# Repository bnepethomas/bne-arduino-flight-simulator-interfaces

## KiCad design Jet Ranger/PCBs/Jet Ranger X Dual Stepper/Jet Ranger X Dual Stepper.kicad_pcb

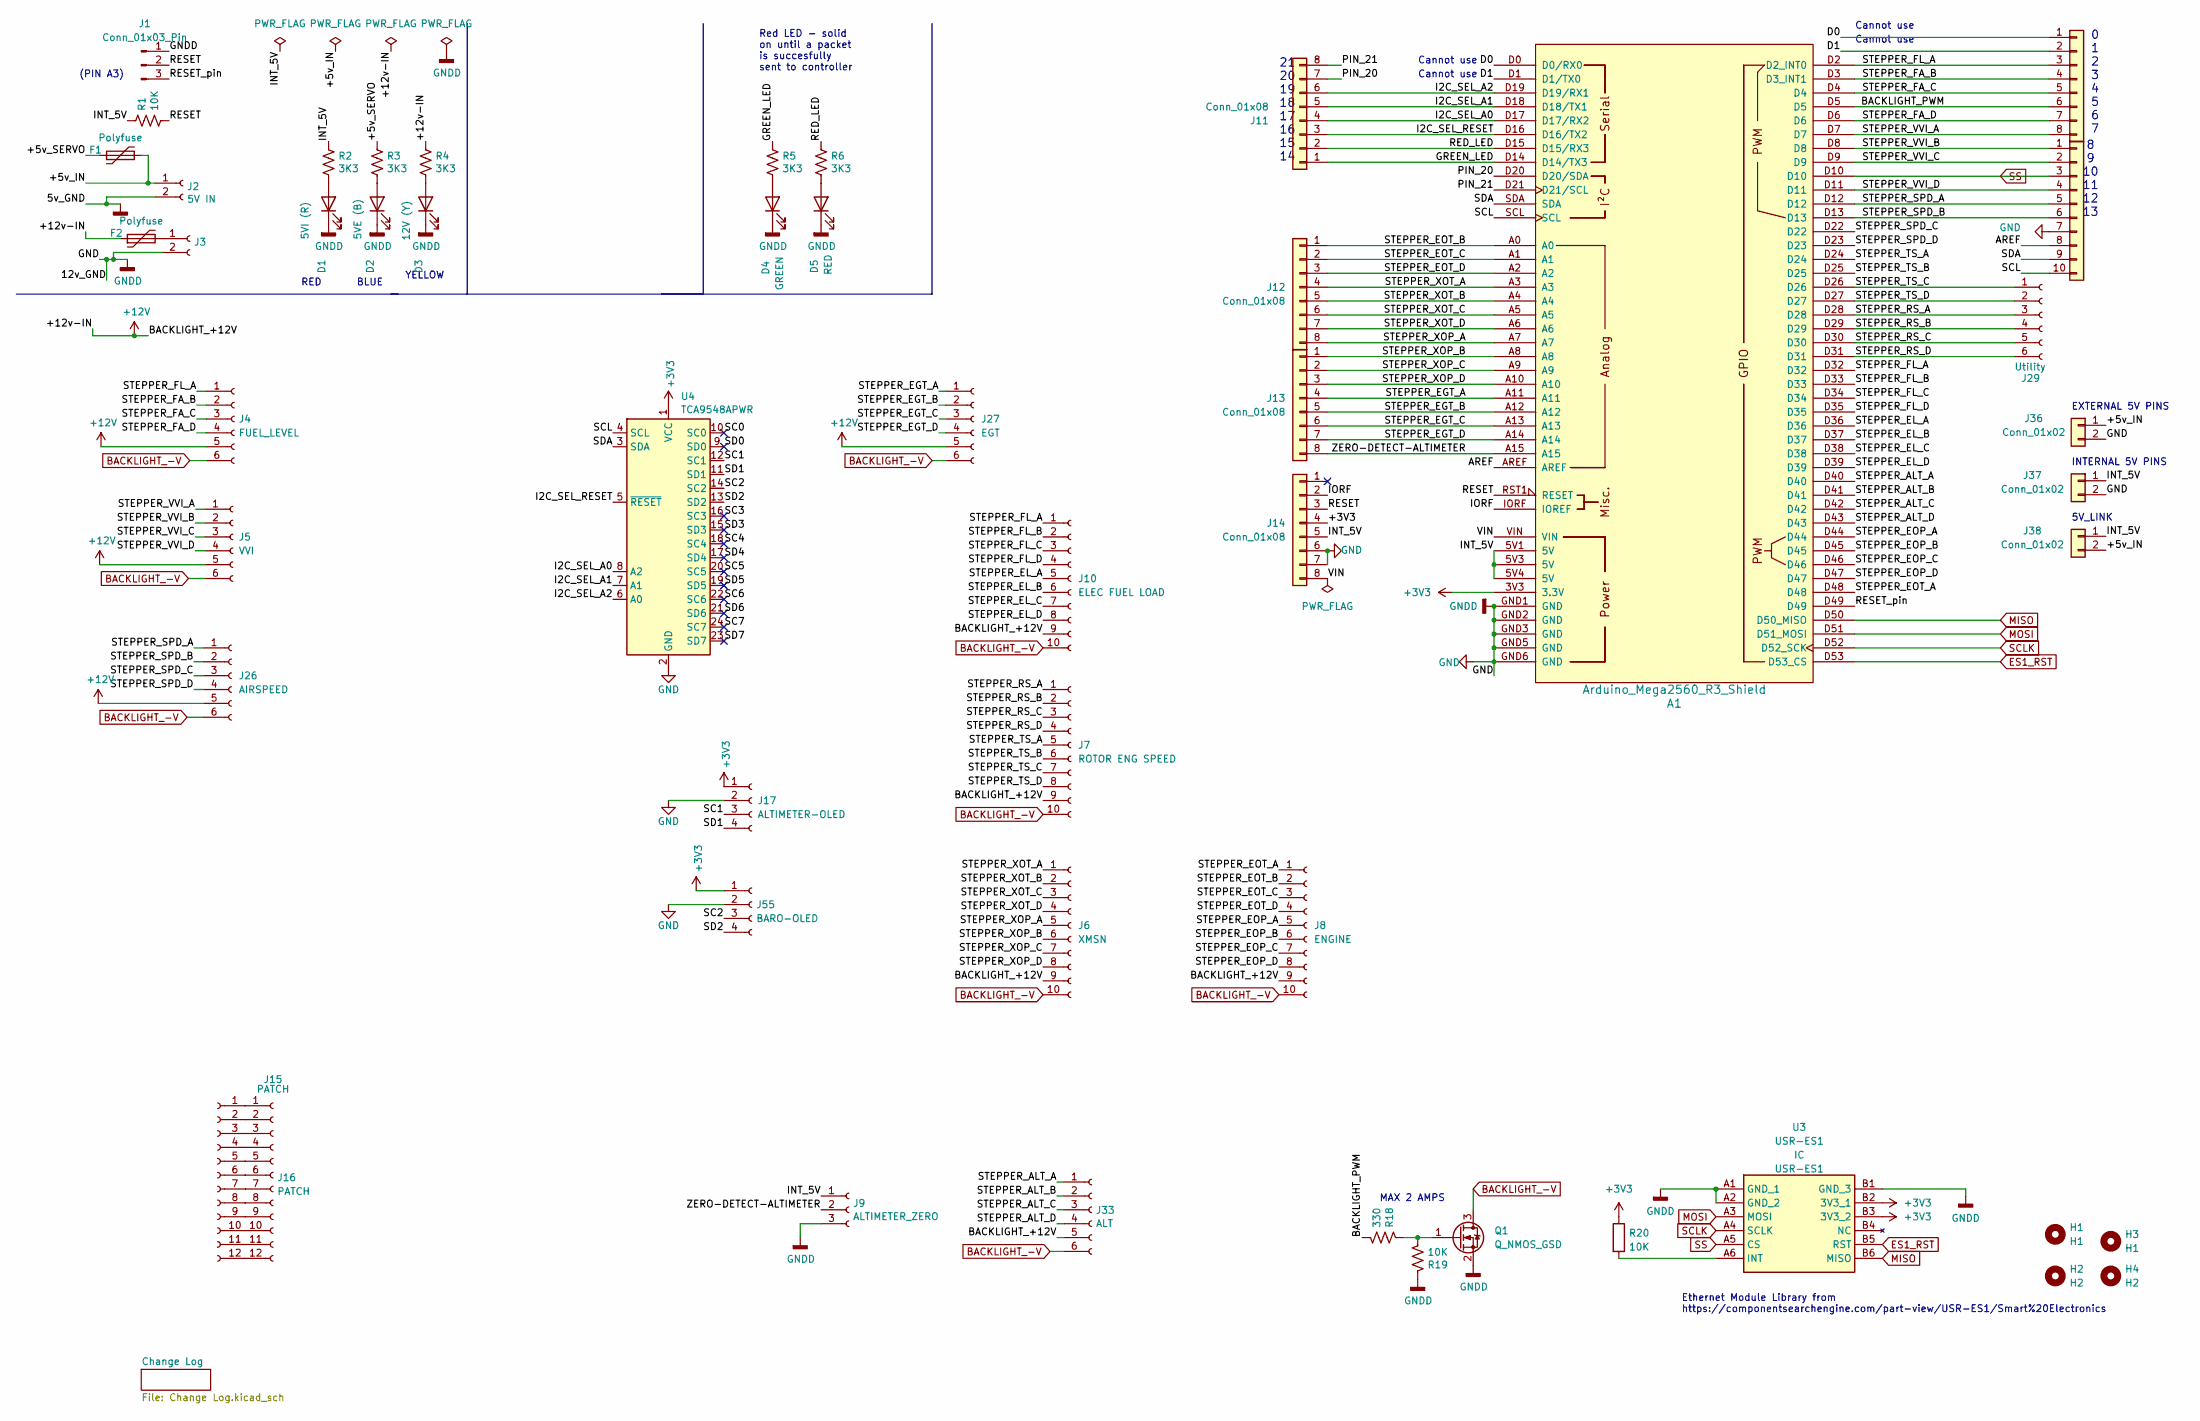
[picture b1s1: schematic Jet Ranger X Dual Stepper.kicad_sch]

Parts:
A1: Arduino_Mega2560_R3_Shield
D1: 5VI (R); LED_D3.0mm
D2: 5VE (B); LED_D3.0mm
D3: 12V (Y); LED_D3.0mm
D4: GREEN; LED_D3.0mm
D5: RED; LED_D3.0mm
F1, F2: Polyfuse; Fuse_Littelfuse_395Series
H1, H3: H1; MountingHole_3.2mm_M3
H2, H4: H2; MountingHole_3.2mm_M3
J1: Conn_01x03_Pin; PinHeader_1x03_P2.54mm_Vertical
J2: 5V IN; BarrelJack_Horizontal
J3: STEPPER IN 12-20VDC; BarrelJack_Horizontal
J4: FUEL_LEVEL; Molex_KK-254_AE-6410-06A_1x06_P2.54mm_Vertical
J5: VVI; Molex_KK-254_AE-6410-06A_1x06_P2.54mm_Vertical
J6: XMSN; Molex_KK-254_AE-6410-10A_1x10_P2.54mm_Vertical
J7: ROTOR ENG SPEED; Molex_KK-254_AE-6410-10A_1x10_P2.54mm_Vertical
J8: ENGINE; Molex_KK-254_AE-6410-10A_1x10_P2.54mm_Vertical
J9: ALTIMETER_ZERO; Molex_KK-254_AE-6410-03A_1x03_P2.54mm_Vertical
J10: ELEC FUEL LOAD; Molex_KK-254_AE-6410-10A_1x10_P2.54mm_Vertical
J11, J12, J13, J14, J34: Conn_01x08; PinHeader_1x08_P2.54mm_Vertical
J15, J16: PATCH; PinSocket_1x12_P2.54mm_Vertical
J17: ALTIMETER-OLED; Molex_KK-254_AE-6410-04A_1x04_P2.54mm_Vertical
J26: AIRSPEED; Molex_KK-254_AE-6410-06A_1x06_P2.54mm_Vertical
J27: EGT; Molex_KK-254_AE-6410-06A_1x06_P2.54mm_Vertical
J29: Utility; PinHeader_1x06_P2.54mm_Vertical
J33: ALT; Molex_KK-254_AE-6410-06A_1x06_P2.54mm_Vertical
J35: Conn_01x10; PinHeader_1x10_P2.54mm_Vertical
J36, J37, J38: Conn_01x02; PinHeader_1x02_P2.54mm_Vertical
J55: BARO-OLED; Molex_KK-254_AE-6410-04A_1x04_P2.54mm_Vertical
Q1: Q_NMOS_GSD; TO-220-3_Vertical
R1, R19, R20: 10K; R_Axial_DIN0207_L6.3mm_D2.5mm_P2.54mm_Vertical
R2, R3, R4, R5, R6: 3K3; R_Axial_DIN0207_L6.3mm_D2.5mm_P2.54mm_Vertical
R18: 330; R_Axial_DIN0207_L6.3mm_D2.5mm_P2.54mm_Vertical
U3: USR-ES1; USRES1; Manufacturer_Part_Number USR-ES1
U4: TCA9548APWR; DIP-24_TCA9548A

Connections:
+3V3: A1.3V3 (3.3V), J14.4, J17.1, J55.1, R20.1, U3.B2 (3V3_1), U3.B3 (3V3_2), U4.1 (VCC)
+12V: F2.1, J4.5, J5.5, J6.9, J7.9, J8.9, J10.9, J26.5, J27.5, J33.5, R4.1
/+5v_IN: F1.2, J2.1, J36.1, J38.2
/+5v_SERVO: F1.1, R3.1
/AREF: A1.AREF, J35.8
/BACKLIGHT_PWM: A1.D5, J34.6, R18.2
/D0: A1.D0 (D0/RX0), J34.1
/D1: A1.D1 (D1/TX0), J34.2
/GREEN_LED: A1.D14 (D14/TX3), J11.1, R5.1
/I2C_SEL_A0: A1.D17 (D17/RX2), J11.4, U4.8 (A2)
/I2C_SEL_A1: A1.D18 (D18/TX1), J11.5, U4.7 (A1)
/I2C_SEL_A2: A1.D19 (D19/RX1), J11.6, U4.6 (A0)
/I2C_SEL_RESET: A1.D16 (D16/TX2), J11.3, U4.5 (~RESET)
/INT_5V: A1.5V1 (5V), A1.5V3 (5V), A1.5V4 (5V), J9.1, J14.5, J37.1, J38.1, R1.1, R2.1
/IORF: A1.IORF (IOREF), J14.2
/PIN_20: A1.D20 (D20/SDA), J11.7
/PIN_21: A1.D21 (D21/SCL), J11.8
/RED_LED: A1.D15 (D15/RX3), J11.2, R6.1
/RESET: A1.RST1 (RESET), J1.2, J14.3, R1.2
/RESET_pin: A1.D49, J1.3
/SC0: U4.10 (SC0)
/SC1: J17.3, U4.12 (SC1)
/SC2: J55.3, U4.14 (SC2)
/SC3: U4.16 (SC3)
/SC4: U4.18 (SC4)
/SC5: U4.20 (SC5)
/SC6: U4.22 (SC6)
/SC7: U4.24 (SC7)
/SCL: A1.SCL, J35.10, U4.4 (SCL)
/SD0: U4.9 (SD0)
/SD1: J17.4, U4.11 (SD1)
/SD2: J55.4, U4.13 (SD2)
/SD3: U4.15 (SD3)
/SD4: U4.17 (SD4)
/SD5: U4.19 (SD5)
/SD6: U4.21 (SD6)
/SD7: U4.23 (SD7)
/SDA: A1.SDA, J35.9, U4.3 (SDA)
/STEPPER_ALT_A: A1.D40, J33.1
/STEPPER_ALT_B: A1.D41, J33.2
/STEPPER_ALT_C: A1.D42, J33.3
/STEPPER_ALT_D: A1.D43, J33.4
/STEPPER_EGT_A: A1.A11, J13.4, J27.1
/STEPPER_EGT_B: A1.A12, J13.5, J27.2
/STEPPER_EGT_C: A1.A13, J13.6, J27.3
/STEPPER_EGT_D: A1.A14, J13.7, J27.4
/STEPPER_EL_A: A1.D36, J10.5
/STEPPER_EL_B: A1.D37, J10.6
/STEPPER_EL_C: A1.D38, J10.7
/STEPPER_EL_D: A1.D39, J10.8
/STEPPER_EOP_A: A1.D44, J8.5
/STEPPER_EOP_B: A1.D45, J8.6
/STEPPER_EOP_C: A1.D46, J8.7
/STEPPER_EOP_D: A1.D47, J8.8
/STEPPER_EOT_A: A1.D48, J8.1
/STEPPER_EOT_B: A1.A0, J8.2, J12.1
/STEPPER_EOT_C: A1.A1, J8.3, J12.2
/STEPPER_EOT_D: A1.A2, J8.4, J12.3
/STEPPER_FA_B: A1.D3 (D3_INT1), J4.2, J34.4
/STEPPER_FA_C: A1.D4, J4.3, J34.5
/STEPPER_FA_D: A1.D6, J4.4, J34.7
/STEPPER_FL_A: A1.D2 (D2_INT0), A1.D32, J4.1, J10.1, J34.3
/STEPPER_FL_B: A1.D33, J10.2
/STEPPER_FL_C: A1.D34, J10.3
/STEPPER_FL_D: A1.D35, J10.4
/STEPPER_RS_A: A1.D28, J7.1, J29.3
/STEPPER_RS_B: A1.D29, J7.2, J29.4
/STEPPER_RS_C: A1.D30, J7.3, J29.5
/STEPPER_RS_D: A1.D31, J7.4, J29.6
/STEPPER_SPD_A: A1.D12, J26.1, J35.5
/STEPPER_SPD_B: A1.D13, J26.2, J35.6
/STEPPER_SPD_C: A1.D22, J26.3
/STEPPER_SPD_D: A1.D23, J26.4
/STEPPER_TS_A: A1.D24, J7.5
/STEPPER_TS_B: A1.D25, J7.6
/STEPPER_TS_C: A1.D26, J7.7, J29.1
/STEPPER_TS_D: A1.D27, J7.8, J29.2
/STEPPER_VVI_A: A1.D7, J5.1, J34.8
/STEPPER_VVI_B: A1.D8, J5.2, J35.1
/STEPPER_VVI_C: A1.D9, J5.3, J35.2
/STEPPER_VVI_D: A1.D11, J5.4, J35.4
/STEPPER_XOP_A: A1.A7, J6.5, J12.8
/STEPPER_XOP_B: A1.A8, J6.6, J13.1
/STEPPER_XOP_C: A1.A9, J6.7, J13.2
/STEPPER_XOP_D: A1.A10, J6.8, J13.3
/STEPPER_XOT_A: A1.A3, J6.1, J12.4
/STEPPER_XOT_B: A1.A4, J6.2, J12.5
/STEPPER_XOT_C: A1.A5, J6.3, J12.6
/STEPPER_XOT_D: A1.A6, J6.4, J12.7
/VIN: A1.VIN, J14.8
/ZERO-DETECT-ALTIMETER: A1.A15, J9.2, J13.8
BACKLIGHT_-V: J4.6, J5.6, J6.10, J7.10, J8.10, J10.10, J26.6, J27.6, J33.6, Q1.3 (D)
ES1_RST: A1.D53 (D53_CS), U3.B5 (RST)
GND: A1.GND1 (GND), A1.GND2 (GND), A1.GND3 (GND), A1.GND5 (GND), A1.GND6 (GND), D1.1 (K), D2.1 (K), D3.1 (K), D4.1 (K), D5.1 (K), J1.1, J2.2, J3.2, J9.3, J14.6, J14.7, J17.2, J35.7, J36.2, J37.2, J55.2, Q1.2 (S), R19.1, U3.A1 (GND_1), U3.A2 (GND_2), U3.B1 (GND_3), U4.2 (GND)
MISO: A1.D50 (D50_MISO), U3.B6 (MISO)
MOSI: A1.D51 (D51_MOSI), U3.A3 (MOSI)
unnamed: D1.2 (A), R2.2
unnamed: D2.2 (A), R3.2
unnamed: D3.2 (A), R4.2
unnamed: D4.2 (A), R5.2
unnamed: D5.2 (A), R6.2
unnamed: F2.2, J3.1
unnamed: J15.1, J16.1
unnamed: J15.2, J16.2
unnamed: J15.3, J16.3
unnamed: J15.4, J16.4
unnamed: J15.5, J16.5
unnamed: J15.6, J16.6
unnamed: J15.7, J16.7
unnamed: J15.8, J16.8
unnamed: J15.9, J16.9
unnamed: J15.10, J16.10
unnamed: J15.11, J16.11
unnamed: J15.12, J16.12
unnamed: Q1.1 (G), R18.1, R19.2
unnamed: R20.2, U3.A6 (INT)
SCLK: A1.D52 (D52_SCK), U3.A4 (SCLK)
SS: A1.D10, J35.3, U3.A5 (CS)

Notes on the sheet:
YELLOW
MAX 2 AMPS
BLUE
INTERNAL 5V PINS
Ethernet Module Library from https://componentsearchengine.com/part-view/USR-ES1/Smart%20Electronics
Cannot use
RED
(PIN A3)
0 1 2 3 4 5 6 7
Red LED - solid on until a packet is succesfully sent to controller
5V_LINK
21 20 19 18 17 16 15 14
EXTERNAL 5V PINS
8 9 10 11 12 13

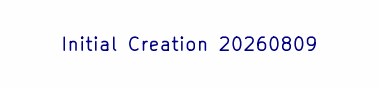
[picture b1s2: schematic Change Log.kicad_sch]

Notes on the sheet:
Initial Creation 20260809

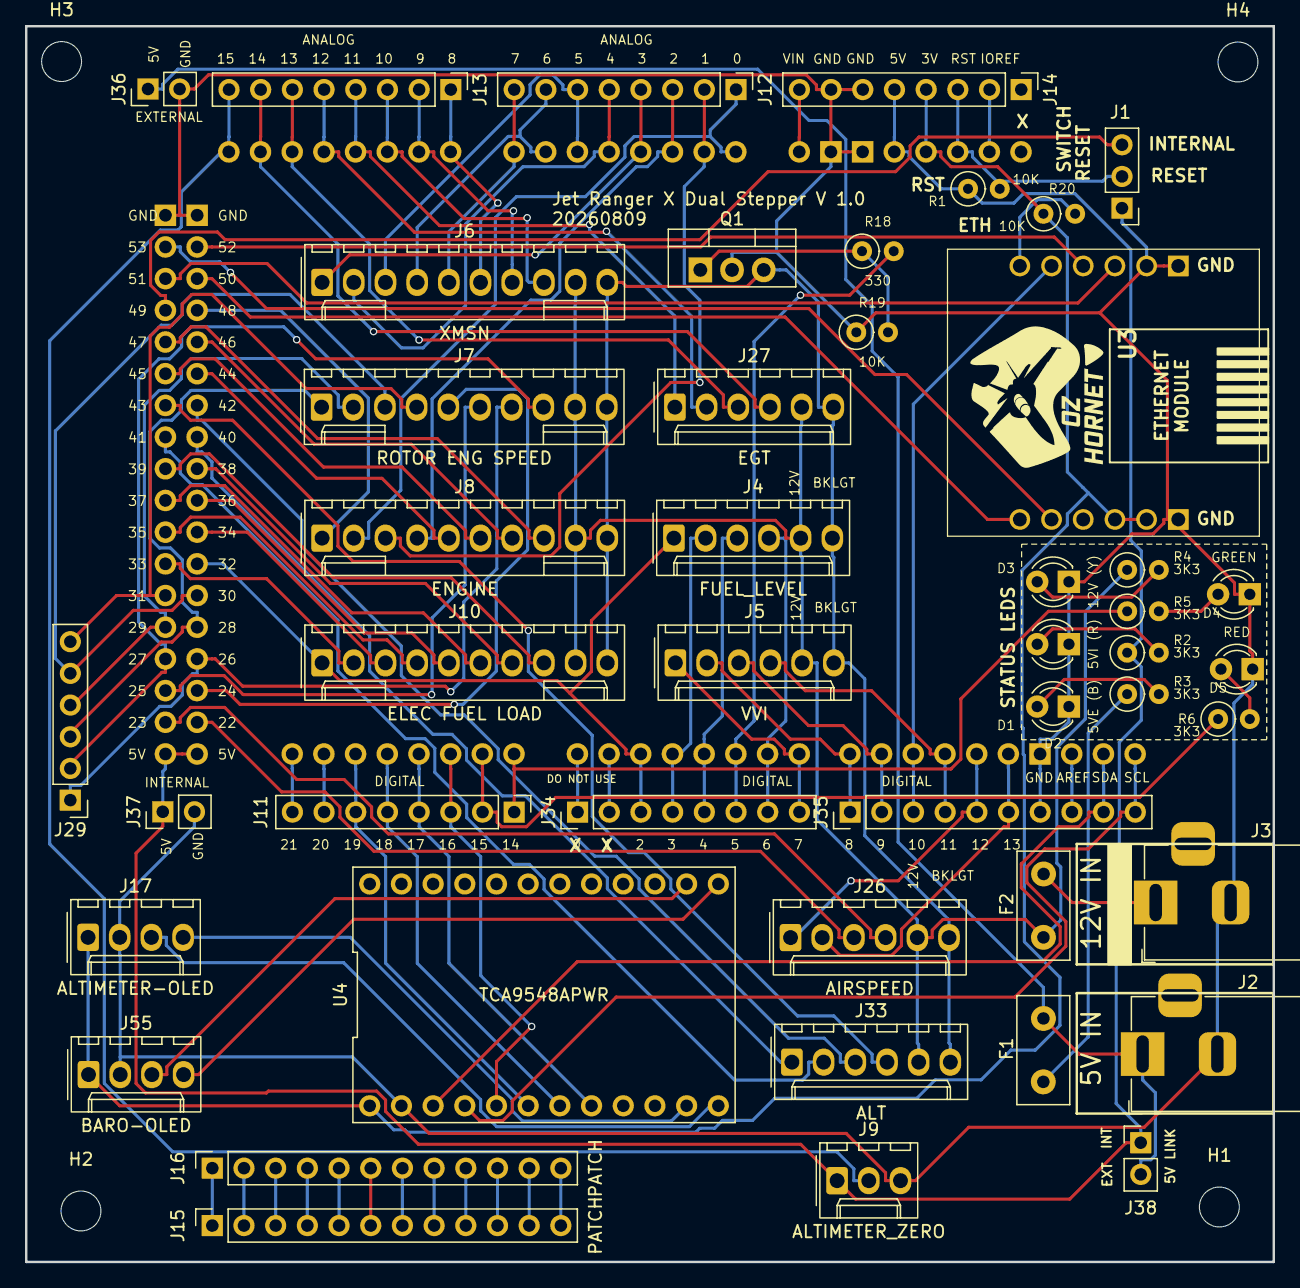
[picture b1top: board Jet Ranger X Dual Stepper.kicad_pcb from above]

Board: 2 copper layers, 100.0 x 99.1 mm, 51 parts (0 on the bottom side), 106 nets.

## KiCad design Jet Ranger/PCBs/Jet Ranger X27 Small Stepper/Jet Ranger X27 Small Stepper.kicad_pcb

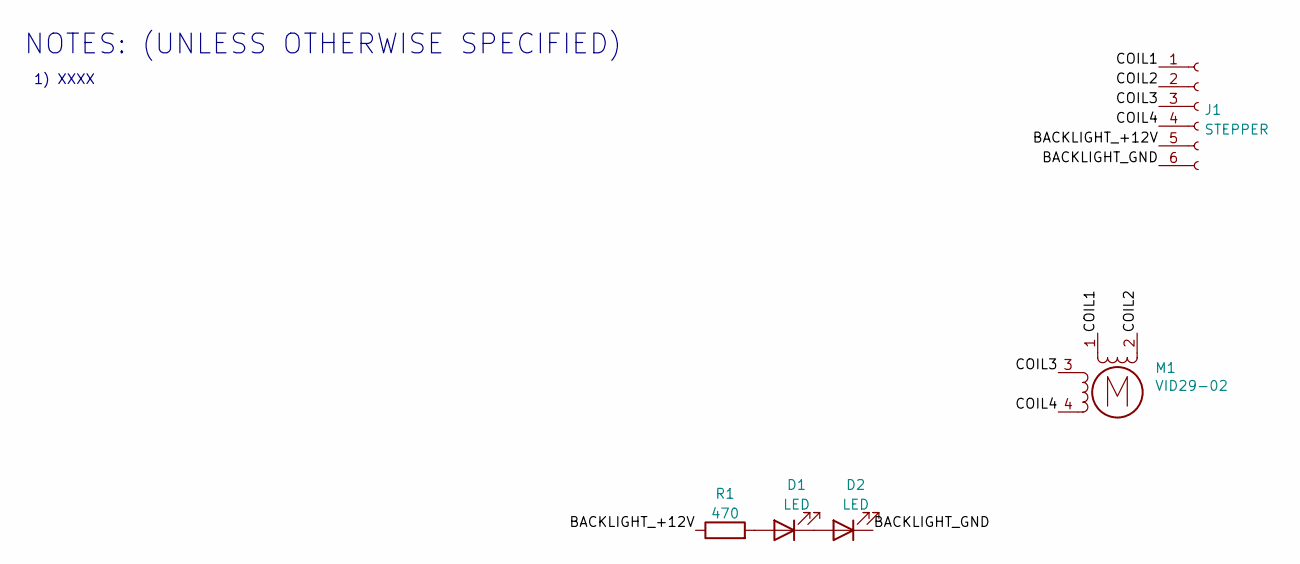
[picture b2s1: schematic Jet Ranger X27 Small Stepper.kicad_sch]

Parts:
D1, D2: LED; LED_D3.0mm
J1: STEPPER; Molex_KK-254_AE-6410-06A_1x06_P2.54mm_Vertical
M1: VID29-02
R1: 470; R_Axial_DIN0204_L3.6mm_D1.6mm_P1.90mm_Vertical

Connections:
/BACKLIGHT_+12V: J1.5, R1.1
/BACKLIGHT_GND: D2.1 (K), J1.6
/COIL1: J1.1, M1.1
/COIL2: J1.2, M1.2 (-)
/COIL3: J1.3, M1.3
/COIL4: J1.4, M1.4
unnamed: D1.2 (A), R1.2
unnamed: D1.1 (K), D2.2 (A)

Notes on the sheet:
1) XXXX
NOTES: (UNLESS OTHERWISE SPECIFIED)

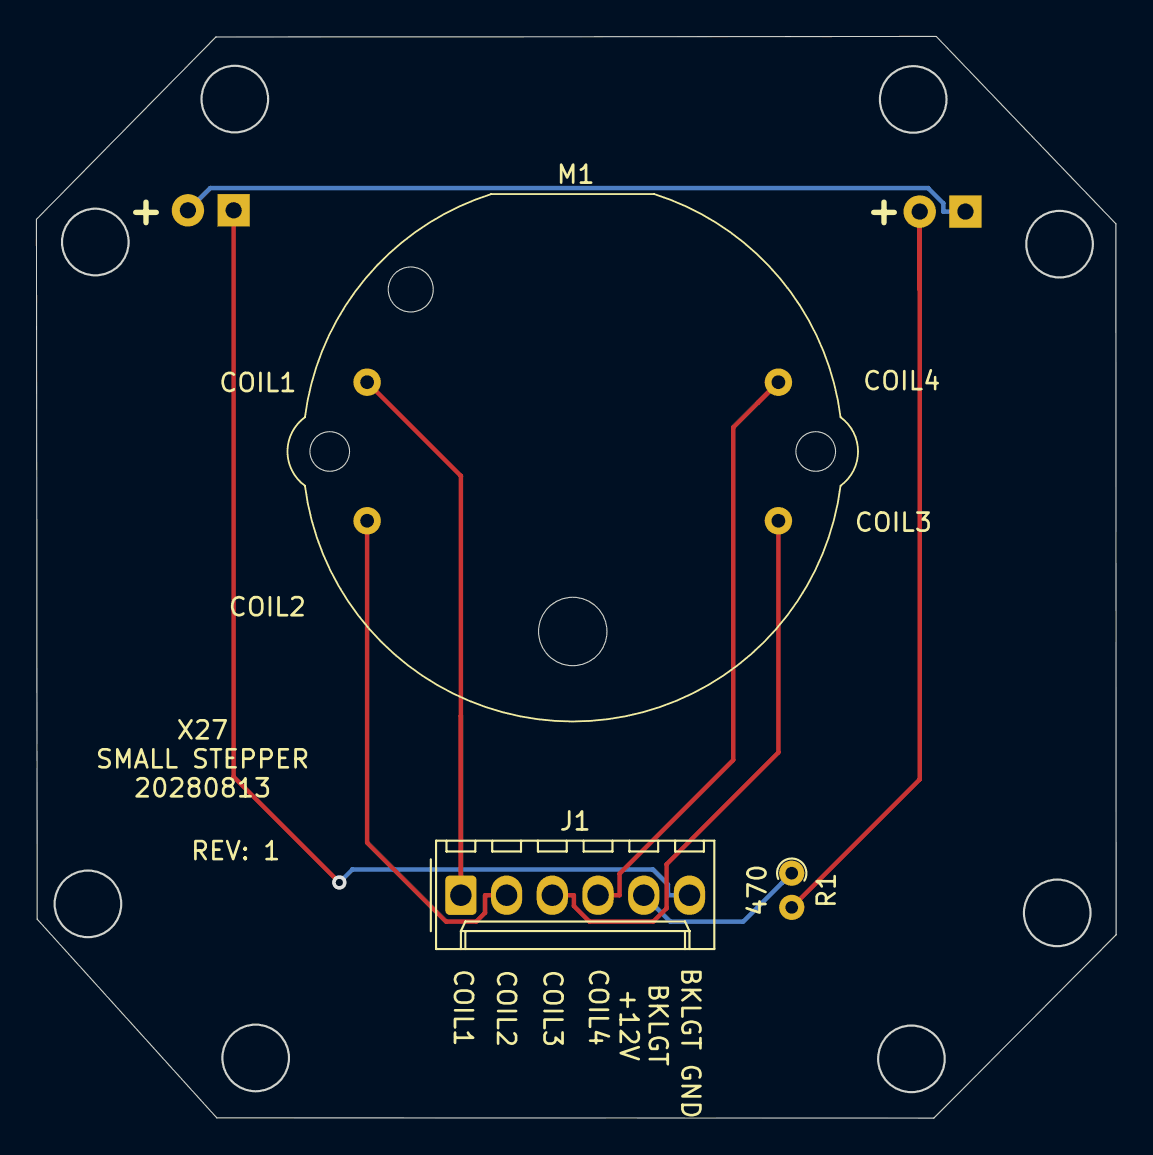
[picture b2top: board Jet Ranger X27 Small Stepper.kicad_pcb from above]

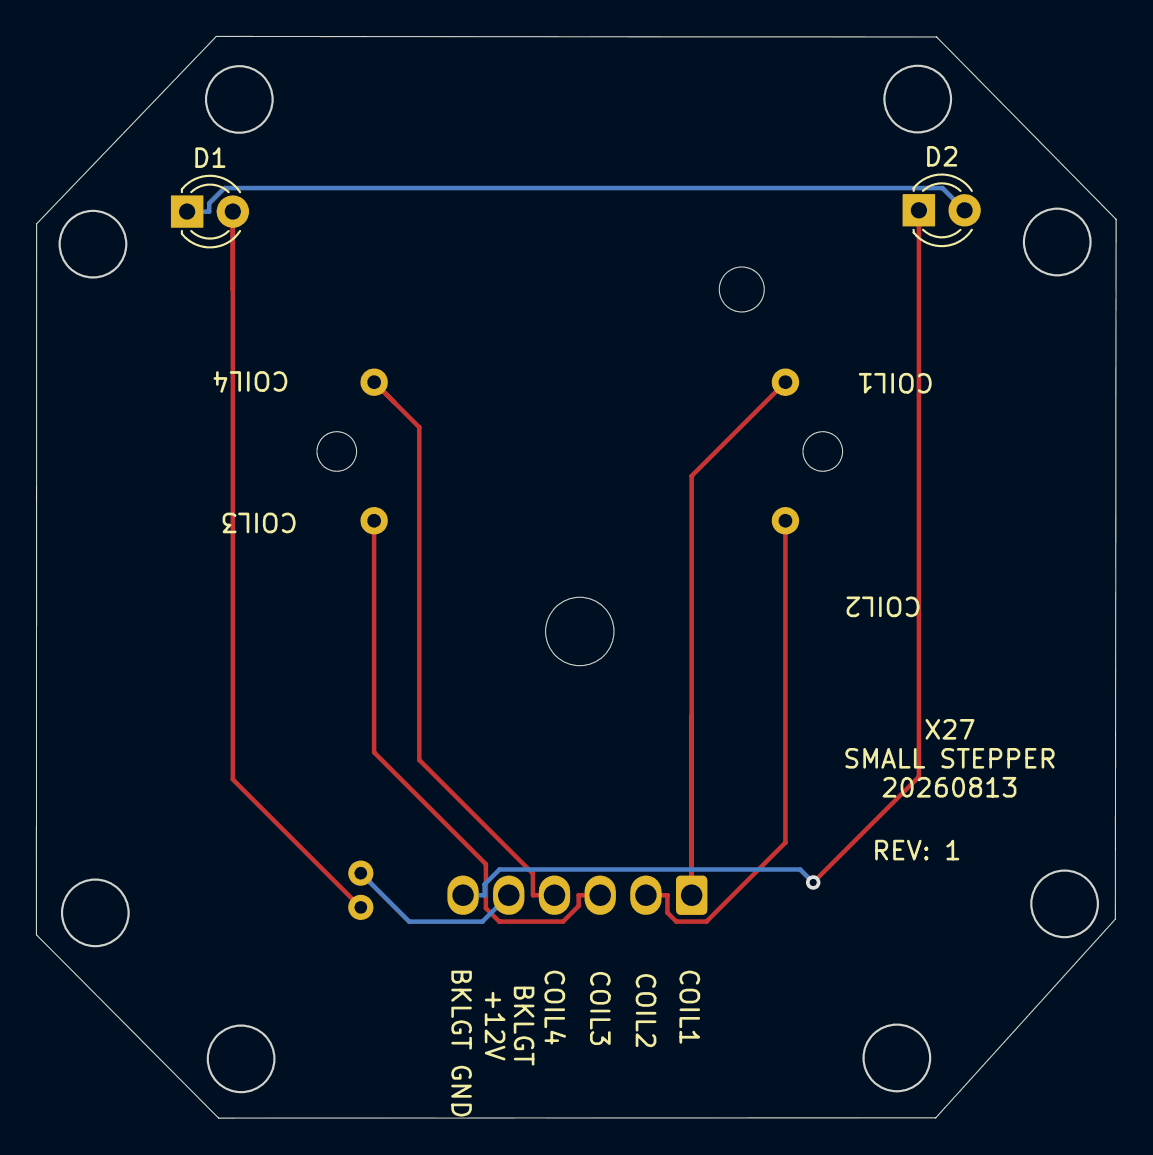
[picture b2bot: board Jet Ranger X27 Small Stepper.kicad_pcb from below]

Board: 2 copper layers, 60.0 x 60.1 mm, 5 parts (2 on the bottom side), 8 nets.

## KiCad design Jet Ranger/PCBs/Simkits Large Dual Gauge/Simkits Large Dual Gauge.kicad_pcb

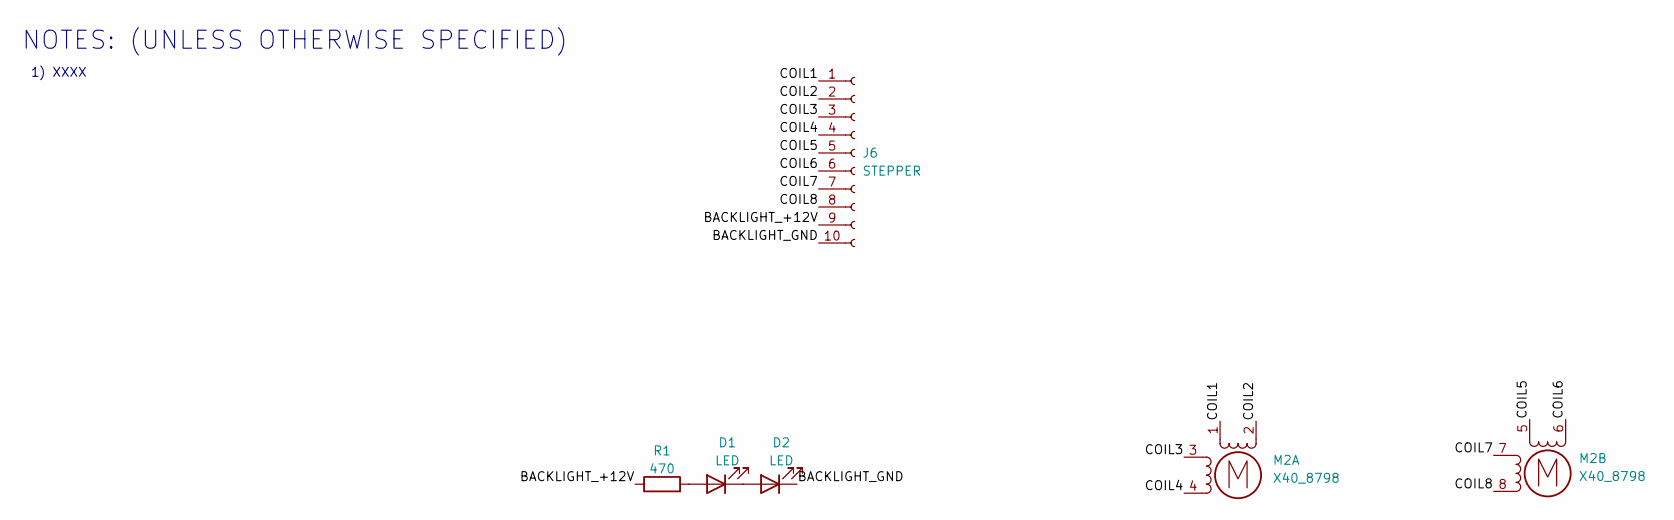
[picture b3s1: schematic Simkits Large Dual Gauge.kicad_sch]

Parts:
D1, D2: LED; LED_D3.0mm
J6: STEPPER; Molex_KK-254_AE-6410-10A_1x10_P2.54mm_Vertical
M2: X40_8798; x40_8798
R1: 470; R_Axial_DIN0204_L3.6mm_D1.6mm_P1.90mm_Vertical

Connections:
/BACKLIGHT_+12V: J6.9, R1.1
/BACKLIGHT_GND: D2.1 (K), J6.10
/COIL1: J6.1, M2.1
/COIL2: J6.2, M2.2 (-)
/COIL3: J6.3, M2.3
/COIL4: J6.4, M2.4
/COIL5: J6.5, M2.5
/COIL6: J6.6, M2.6 (-)
/COIL7: J6.7, M2.7
/COIL8: J6.8, M2.8
unnamed: D1.2 (A), R1.2
unnamed: D1.1 (K), D2.2 (A)

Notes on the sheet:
1) XXXX
NOTES: (UNLESS OTHERWISE SPECIFIED)

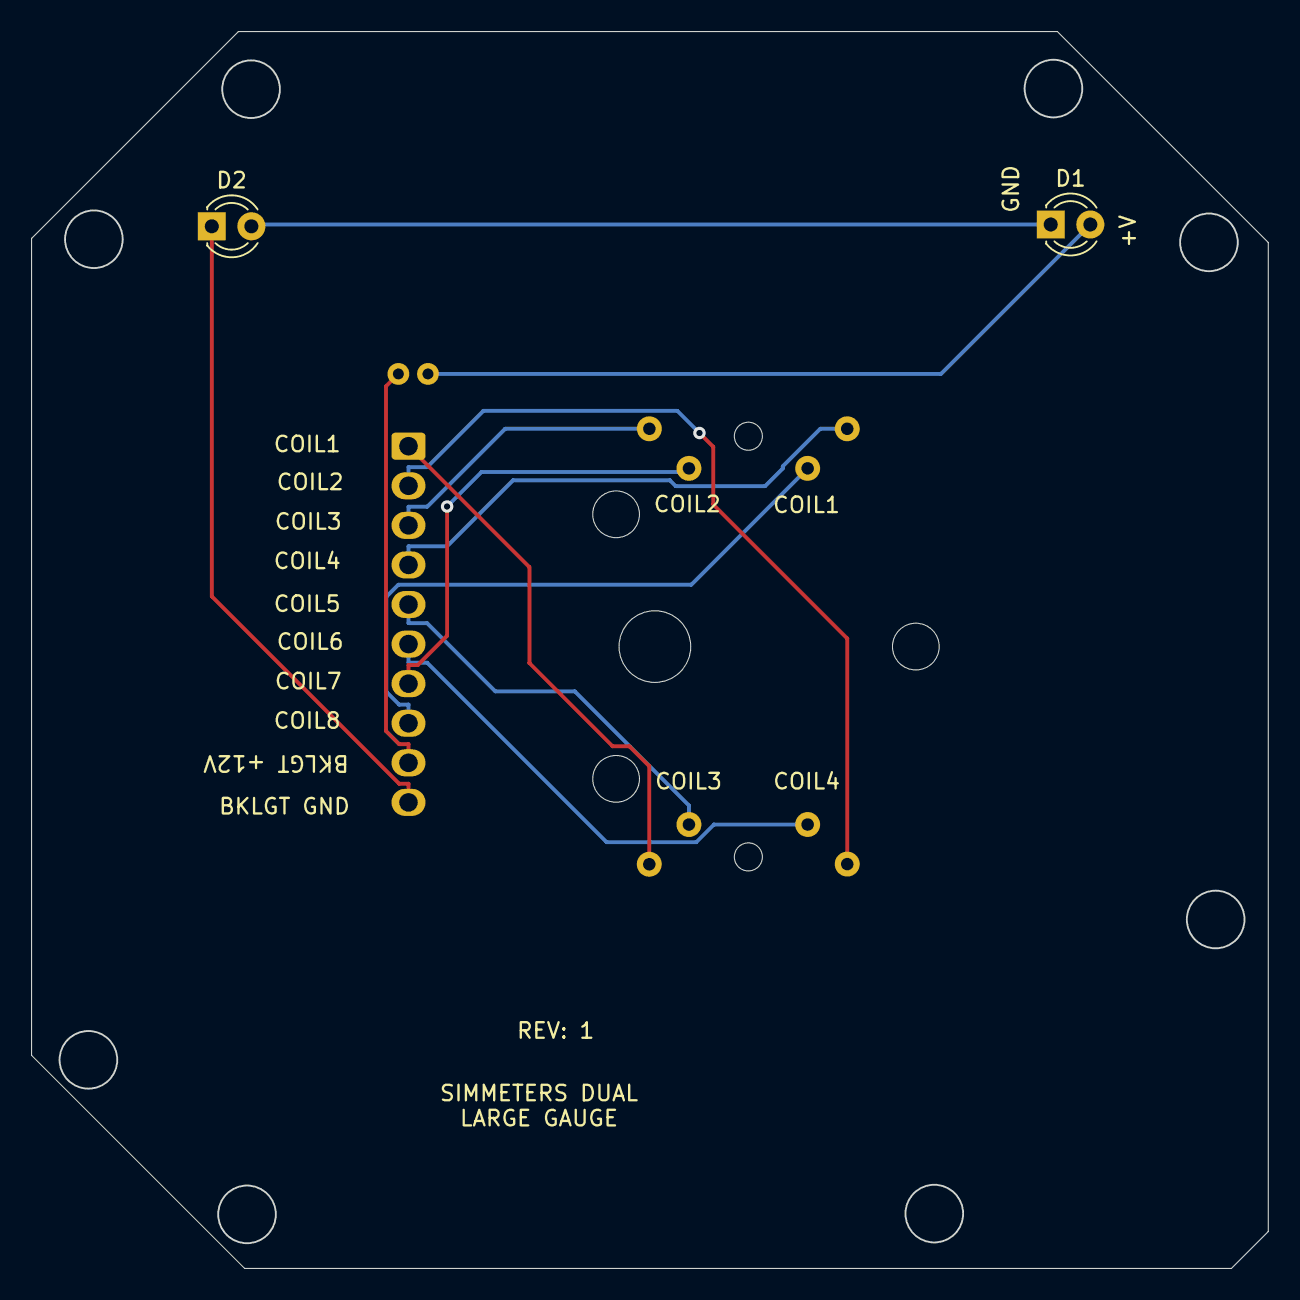
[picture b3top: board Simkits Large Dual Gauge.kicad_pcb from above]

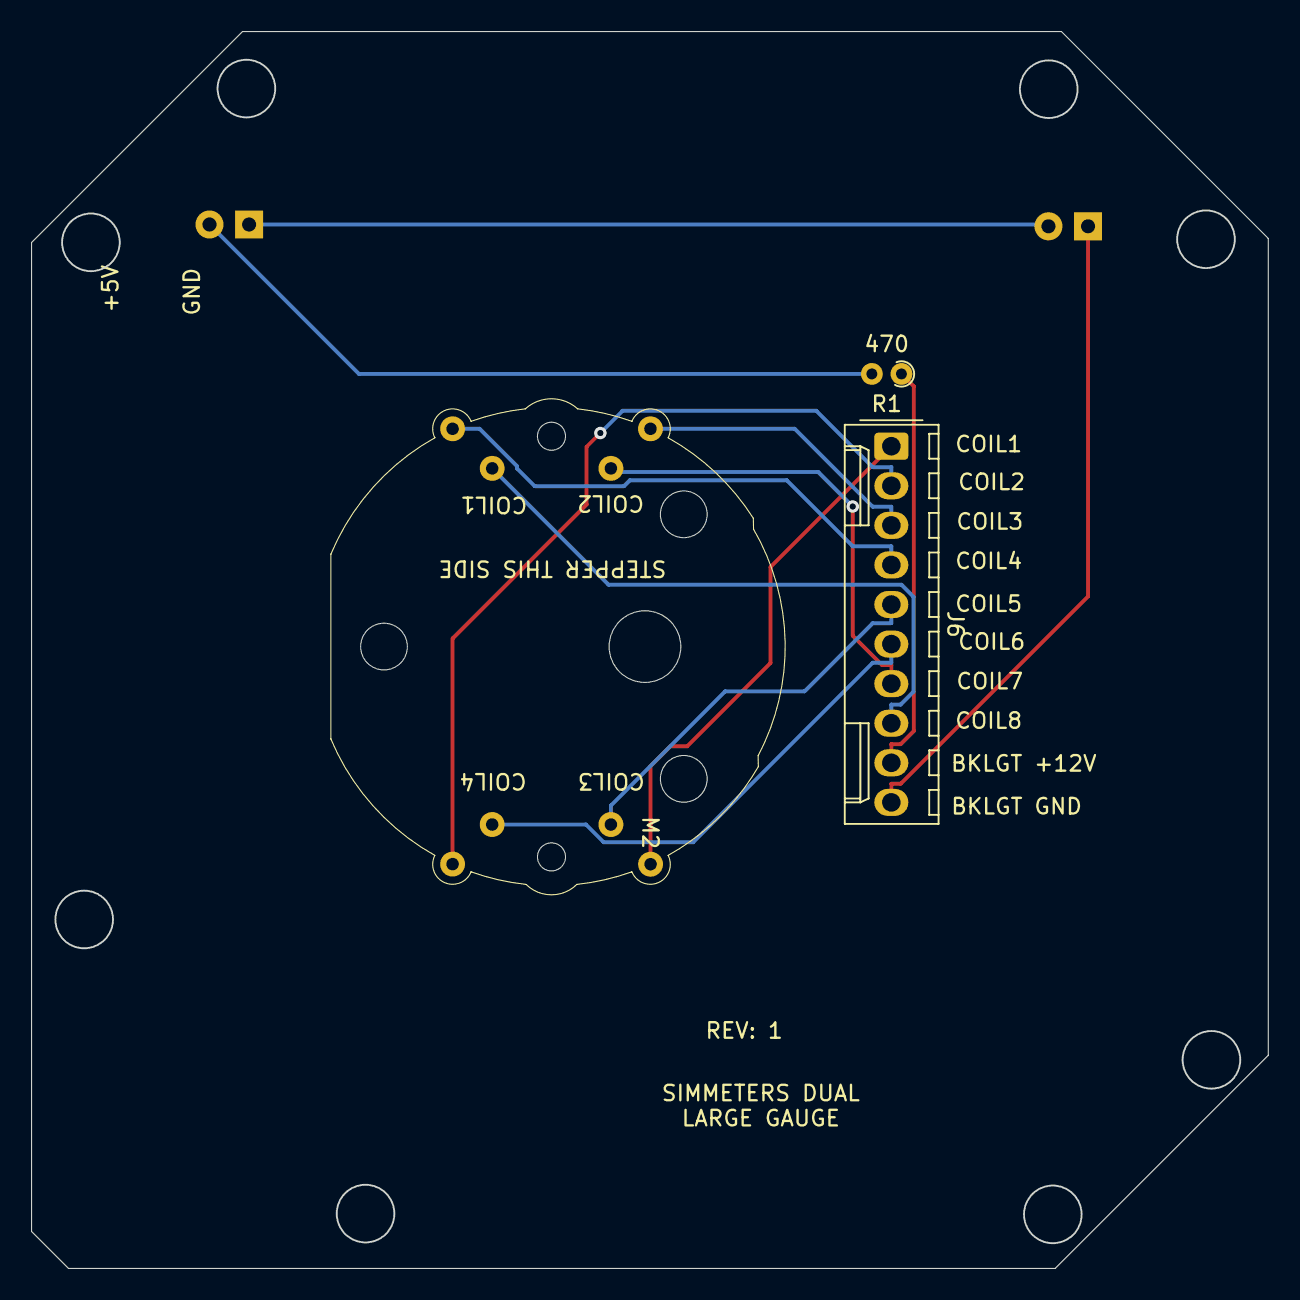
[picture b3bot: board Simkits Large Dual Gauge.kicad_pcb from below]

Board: 2 copper layers, 79.4 x 79.4 mm, 5 parts (2 on the bottom side), 12 nets.

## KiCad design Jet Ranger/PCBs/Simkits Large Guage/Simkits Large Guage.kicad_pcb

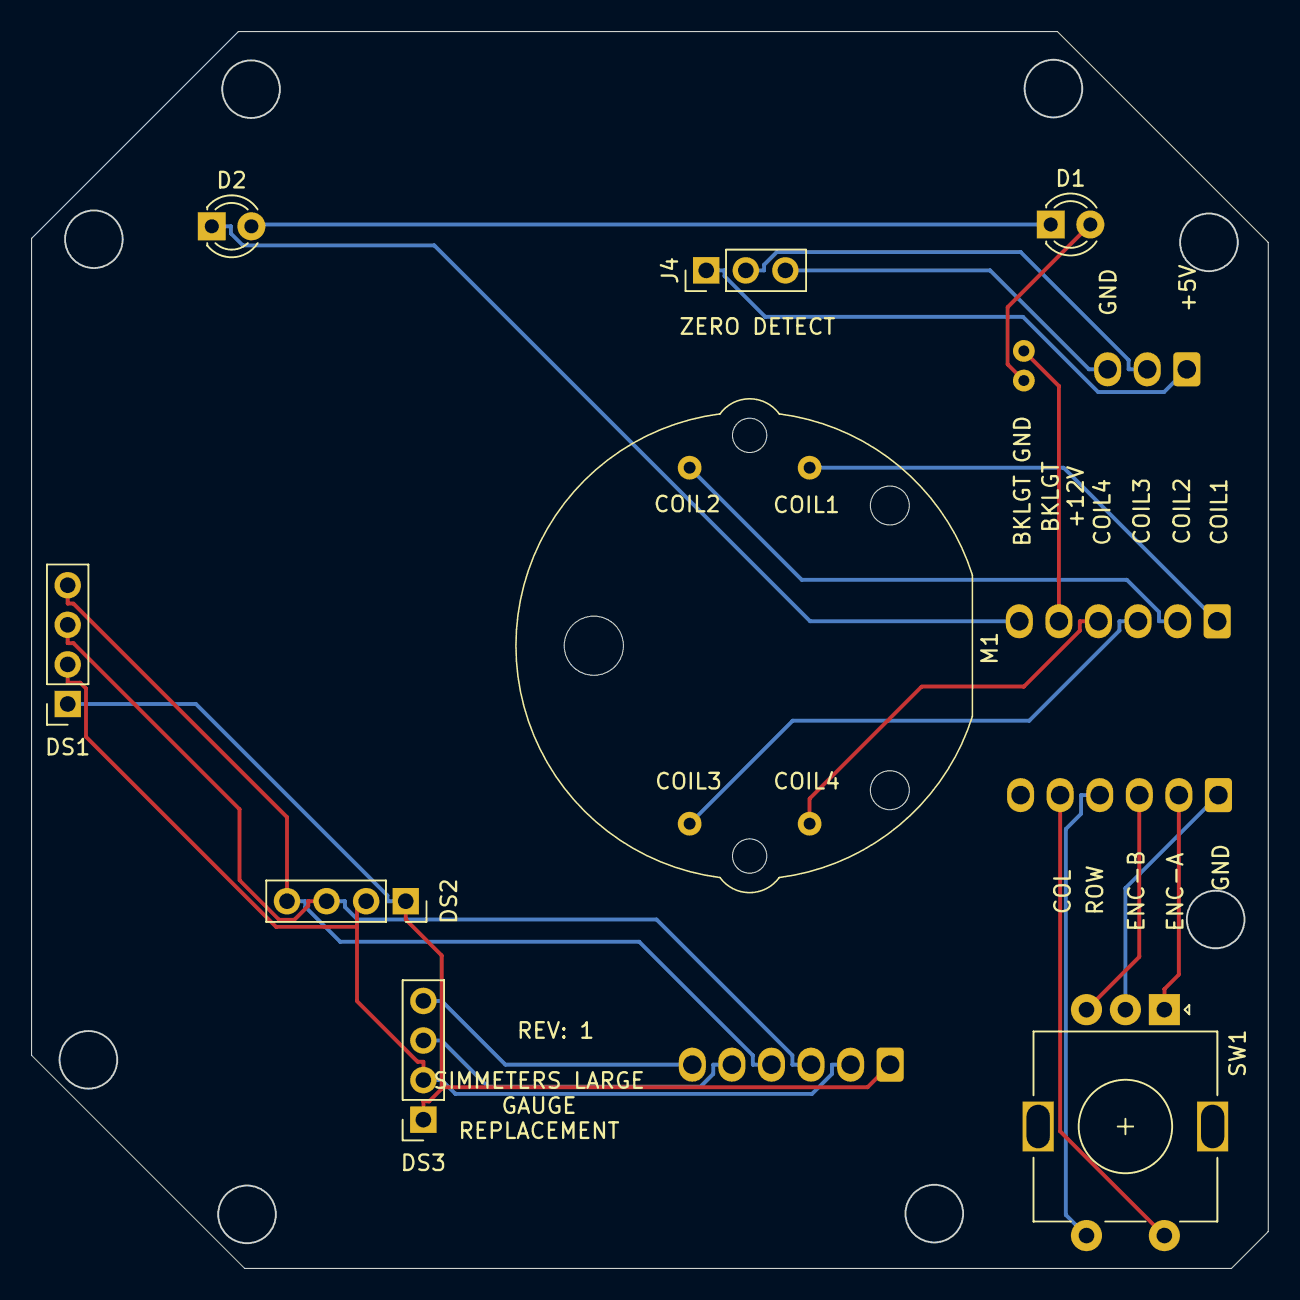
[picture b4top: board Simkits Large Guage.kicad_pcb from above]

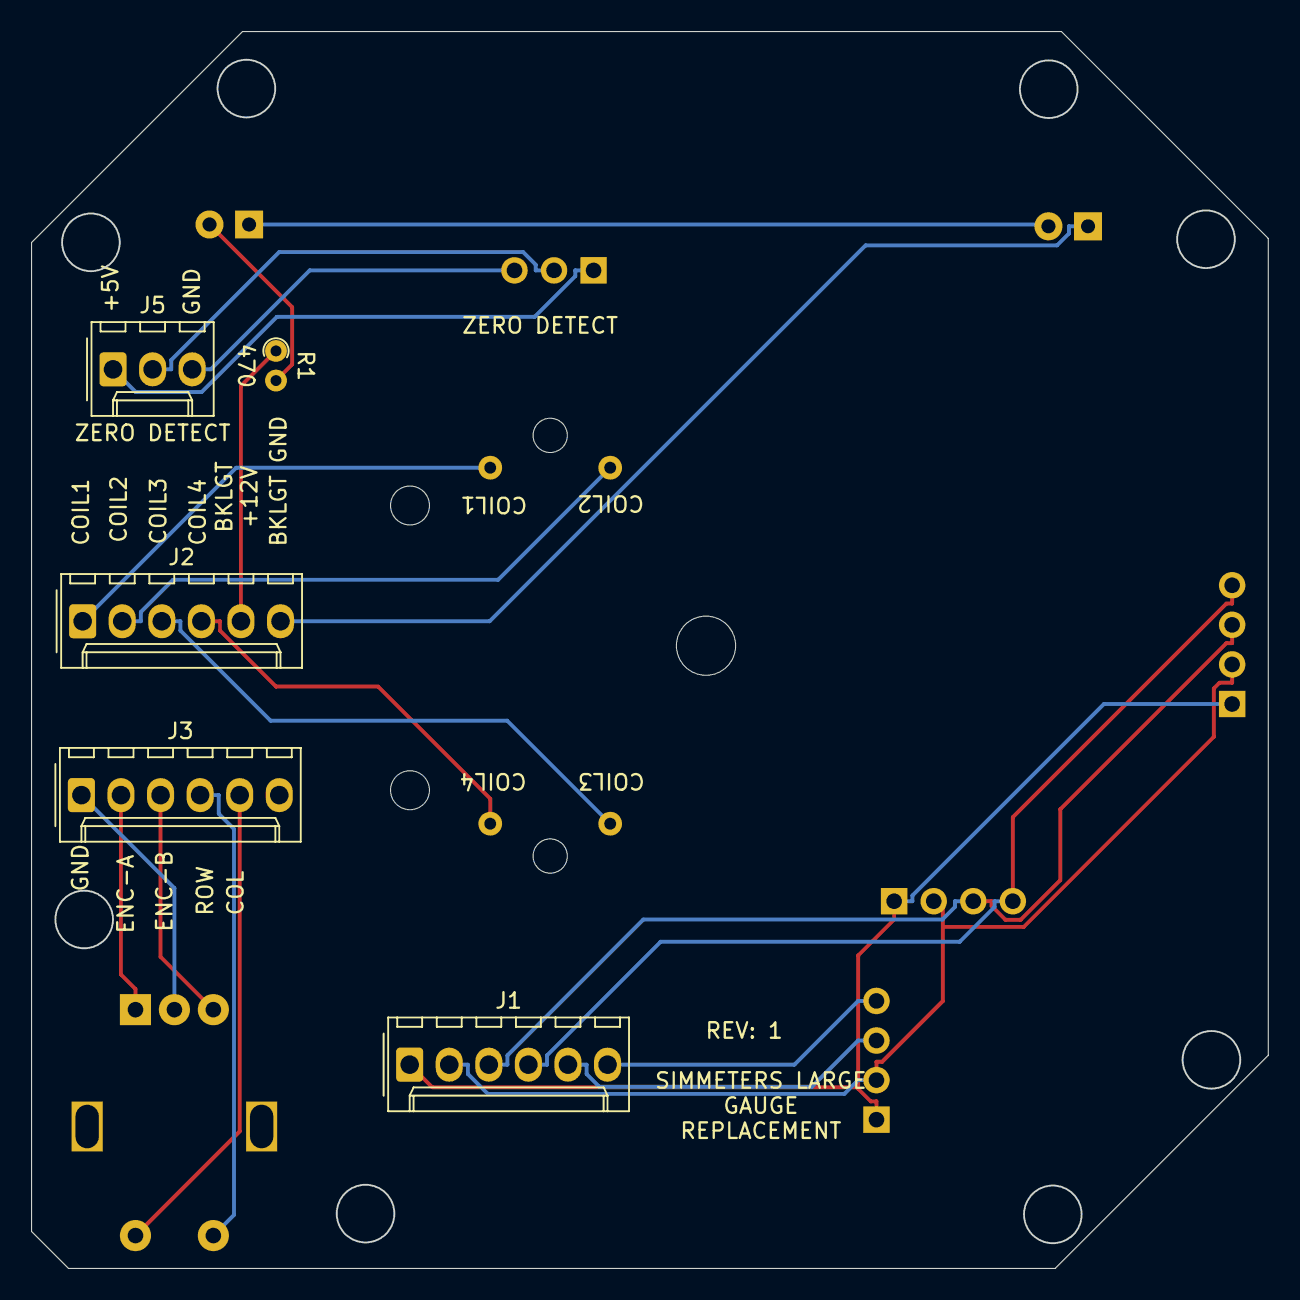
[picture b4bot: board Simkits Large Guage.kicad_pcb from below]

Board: 2 copper layers, 79.4 x 79.4 mm, 13 parts (5 on the bottom side), 22 nets.

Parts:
D1, D2: LED; LED_D3.0mm
DS1, DS2: 10K_ALT_DISP; PinSocket_1x04_P2.54mm_Vertical
DS3: PRESS_DISP; PinSocket_1x04_P2.54mm_Vertical
J1: OLED; Molex_KK-254_AE-6410-06A_1x06_P2.54mm_Vertical
J2: STEPPER; Molex_KK-254_AE-6410-06A_1x06_P2.54mm_Vertical
J3: ENCODER; Molex_KK-254_AE-6410-06A_1x06_P2.54mm_Vertical
J4: ZERO; PinHeader_1x03_P2.54mm_Vertical
J5: ZERO DETECT; Molex_KK-254_AE-6410-03A_1x03_P2.54mm_Vertical
M1: VID29-02
R1: 470; R_Axial_DIN0204_L3.6mm_D1.6mm_P1.90mm_Vertical
SW1: RotaryEncoder_Switch; RotaryEncoder_Alps_EC11E-Switch_Vertical_H20mm

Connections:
+3V3: DS1.2, DS2.2, DS3.2, J1.2
+5V: J4.1, J5.1
/BACKLIGHT_+12V: J2.5, R1.1
/BACKLIGHT_GND: D2.1 (K), J2.6
/COIL1: J2.1, M1.1
/COIL2: J2.2, M1.2 (-)
/COIL3: J2.3, M1.3
/COIL4: J2.4, M1.4
/COL: J3.5, SW1.S2
/ENCODER B: J3.3, SW1.B
/ENCODER-A: J3.2, SW1.A
/ENCORDER GND: J3.1, SW1.C
/ROW: J3.4, SW1.S1
/SC0: DS1.3, DS2.3, J1.3
/SC1: DS3.3, J1.5
/SD0: DS1.4, DS2.4, J1.4
/SD1: DS3.4, J1.6
/ZERO_DETECT: J4.2, J5.2
GND: DS1.1, DS2.1, DS3.1, J1.1
GND1: J4.3, J5.3
unnamed: D1.2 (A), R1.2
unnamed: D1.1 (K), D2.2 (A)

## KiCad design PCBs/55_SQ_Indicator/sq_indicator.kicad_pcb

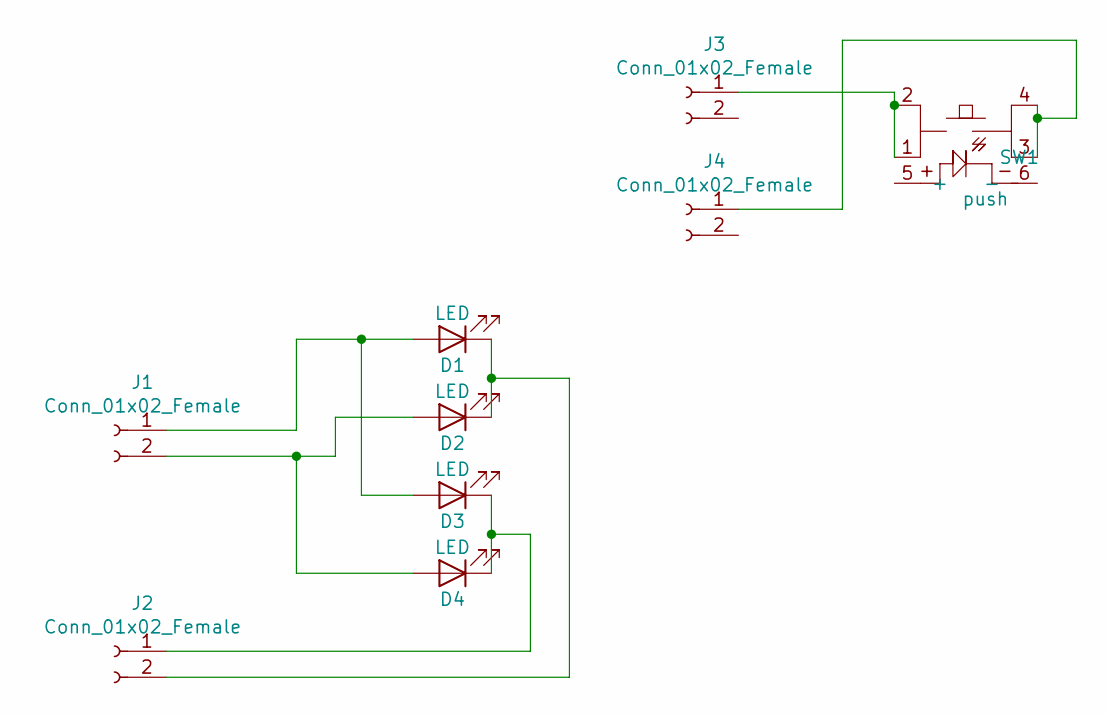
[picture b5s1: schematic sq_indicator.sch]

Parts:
D1, D2, D3, D4: LED; LED_D3.0mm
J1, J2, J3, J4: Conn_01x02_Female; PinHeader_1x02_P2.54mm_Vertical
SW1: push; PT_Small_Tactile_Switch_With_LED

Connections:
unnamed: D1.1 (K), D2.1 (K), J2.2
unnamed: D1.2 (A), D3.2 (A), J1.1
unnamed: D2.2 (A), D4.2 (A), J1.2
unnamed: D3.1 (K), D4.1 (K), J2.1
unnamed: J3.1, SW1.1, SW1.2
unnamed: J4.1, SW1.3, SW1.4

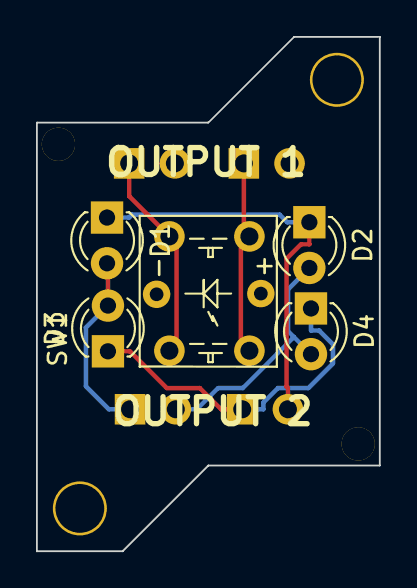
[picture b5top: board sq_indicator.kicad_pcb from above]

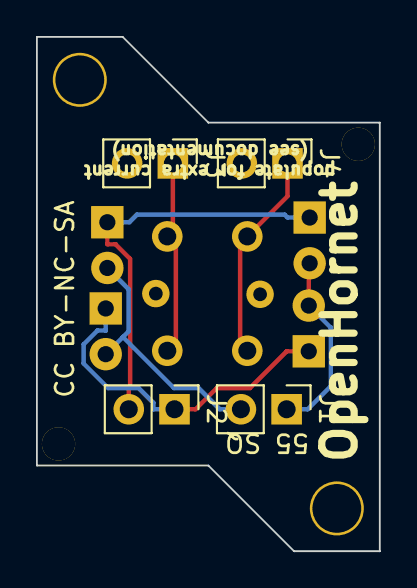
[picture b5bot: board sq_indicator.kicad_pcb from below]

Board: 2 copper layers, 19.1 x 28.6 mm, 13 parts (4 on the bottom side), 6 nets.

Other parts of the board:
H1, H3: Mouting_Hole_1.85mm
H2, H4: Mouting_Hole_2.71mm

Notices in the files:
Jet Ranger/PCBs/Jet Ranger X Dual Stepper/Jet Ranger X Dual Stepper.kicad_pcb:
© OZ HORNET
PCBs/55_SQ_Indicator/sq_indicator.kicad_pcb:
CC BY-NC-SA
